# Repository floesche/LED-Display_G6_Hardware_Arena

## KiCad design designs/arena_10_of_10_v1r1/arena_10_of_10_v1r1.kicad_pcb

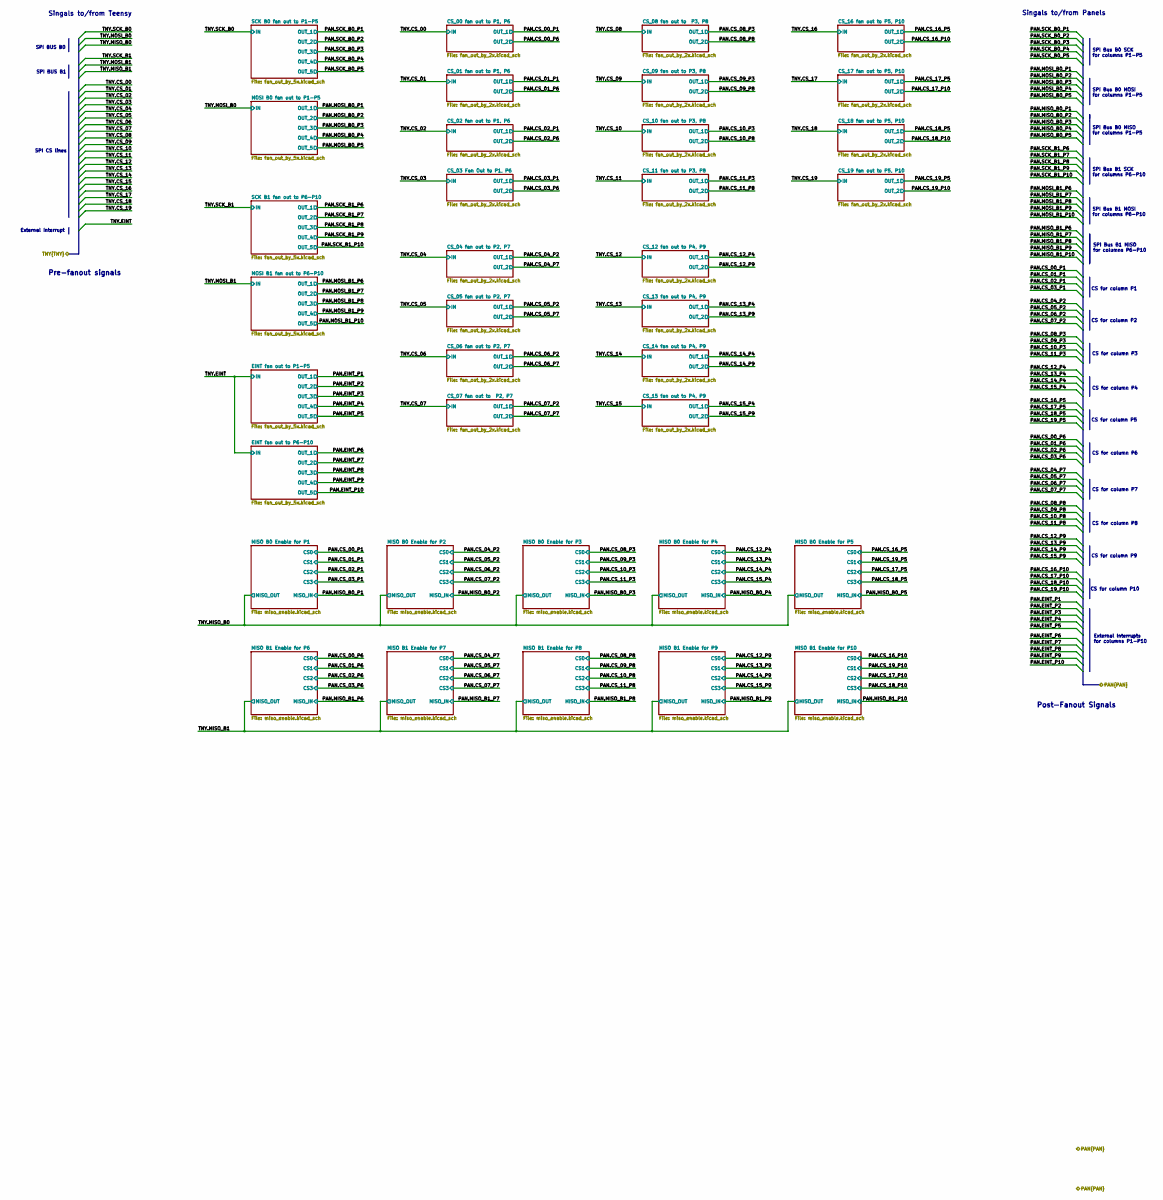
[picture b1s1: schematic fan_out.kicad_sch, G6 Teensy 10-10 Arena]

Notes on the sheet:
Singals to/from Panels
Pre-fanout signals
SPI BUS B0
SPI BUS B1
SPI Bus B1 MOSI for columns P6-P10
SPI Bus B0 SCK for columns P1-P5
SPI Bus B0 MOSI for columns P1-P5
CS for column P1
CS for column P5
CS for column P8
CS for column P3
SPI Bus B1 SCK for columns P6-P10
External Interrupt
External Interrupts for columns P1-P10
CS for column P7
Post-Fanout Signals
CS for column P4
CS for column P10
SPI Bus B0 MISO for columns P1-P5
CS for column P9
CS for column P2
Singals to/from Teensy
SPI Bus B1 MISO for columns P6-P10
SPI CS lines
CS for column P6

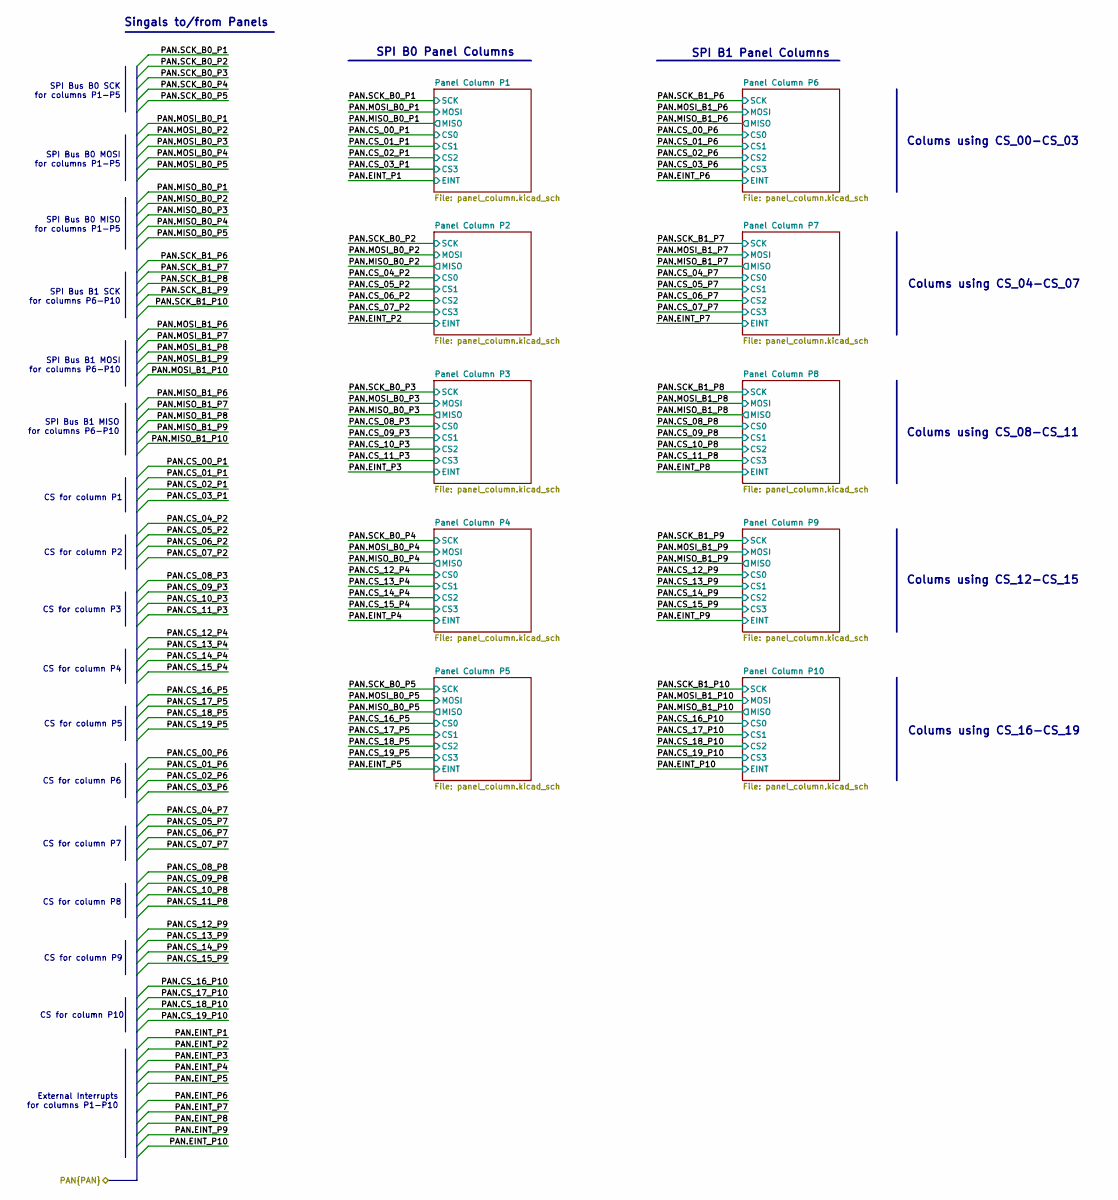
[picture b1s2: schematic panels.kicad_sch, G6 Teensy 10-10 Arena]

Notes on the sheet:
CS for column P2
CS for column P9
SPI Bus B1 MOSI for columns P6-P10
SPI B0 Panel Columns
Colums using CS_00-CS_03
SPI B1 Panel Columns
CS for column P4
SPI Bus B0 MISO for columns P1-P5
SPI Bus B0 MOSI for columns P1-P5
SPI Bus B1 MISO for columns P6-P10
CS for column P7
SPI Bus B0 SCK for columns P1-P5
CS for column P10
Colums using CS_08-CS_11
CS for column P3
Colums using CS_16-CS_19
CS for column P6
Colums using CS_12-CS_15
Colums using CS_04-CS_07
SPI Bus B1 SCK for columns P6-P10
External Interrupts for columns P1-P10
Singals to/from Panels
CS for column P8
CS for column P5
CS for column P1

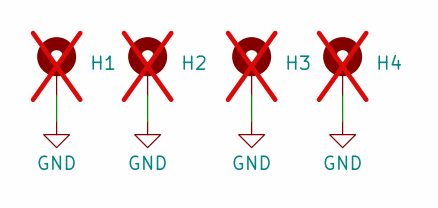
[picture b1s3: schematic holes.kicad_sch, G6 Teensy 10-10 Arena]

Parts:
H1, H2, H3, H4: MountingHole_Pad; MountingHole_4.5mm_Pad; not fitted

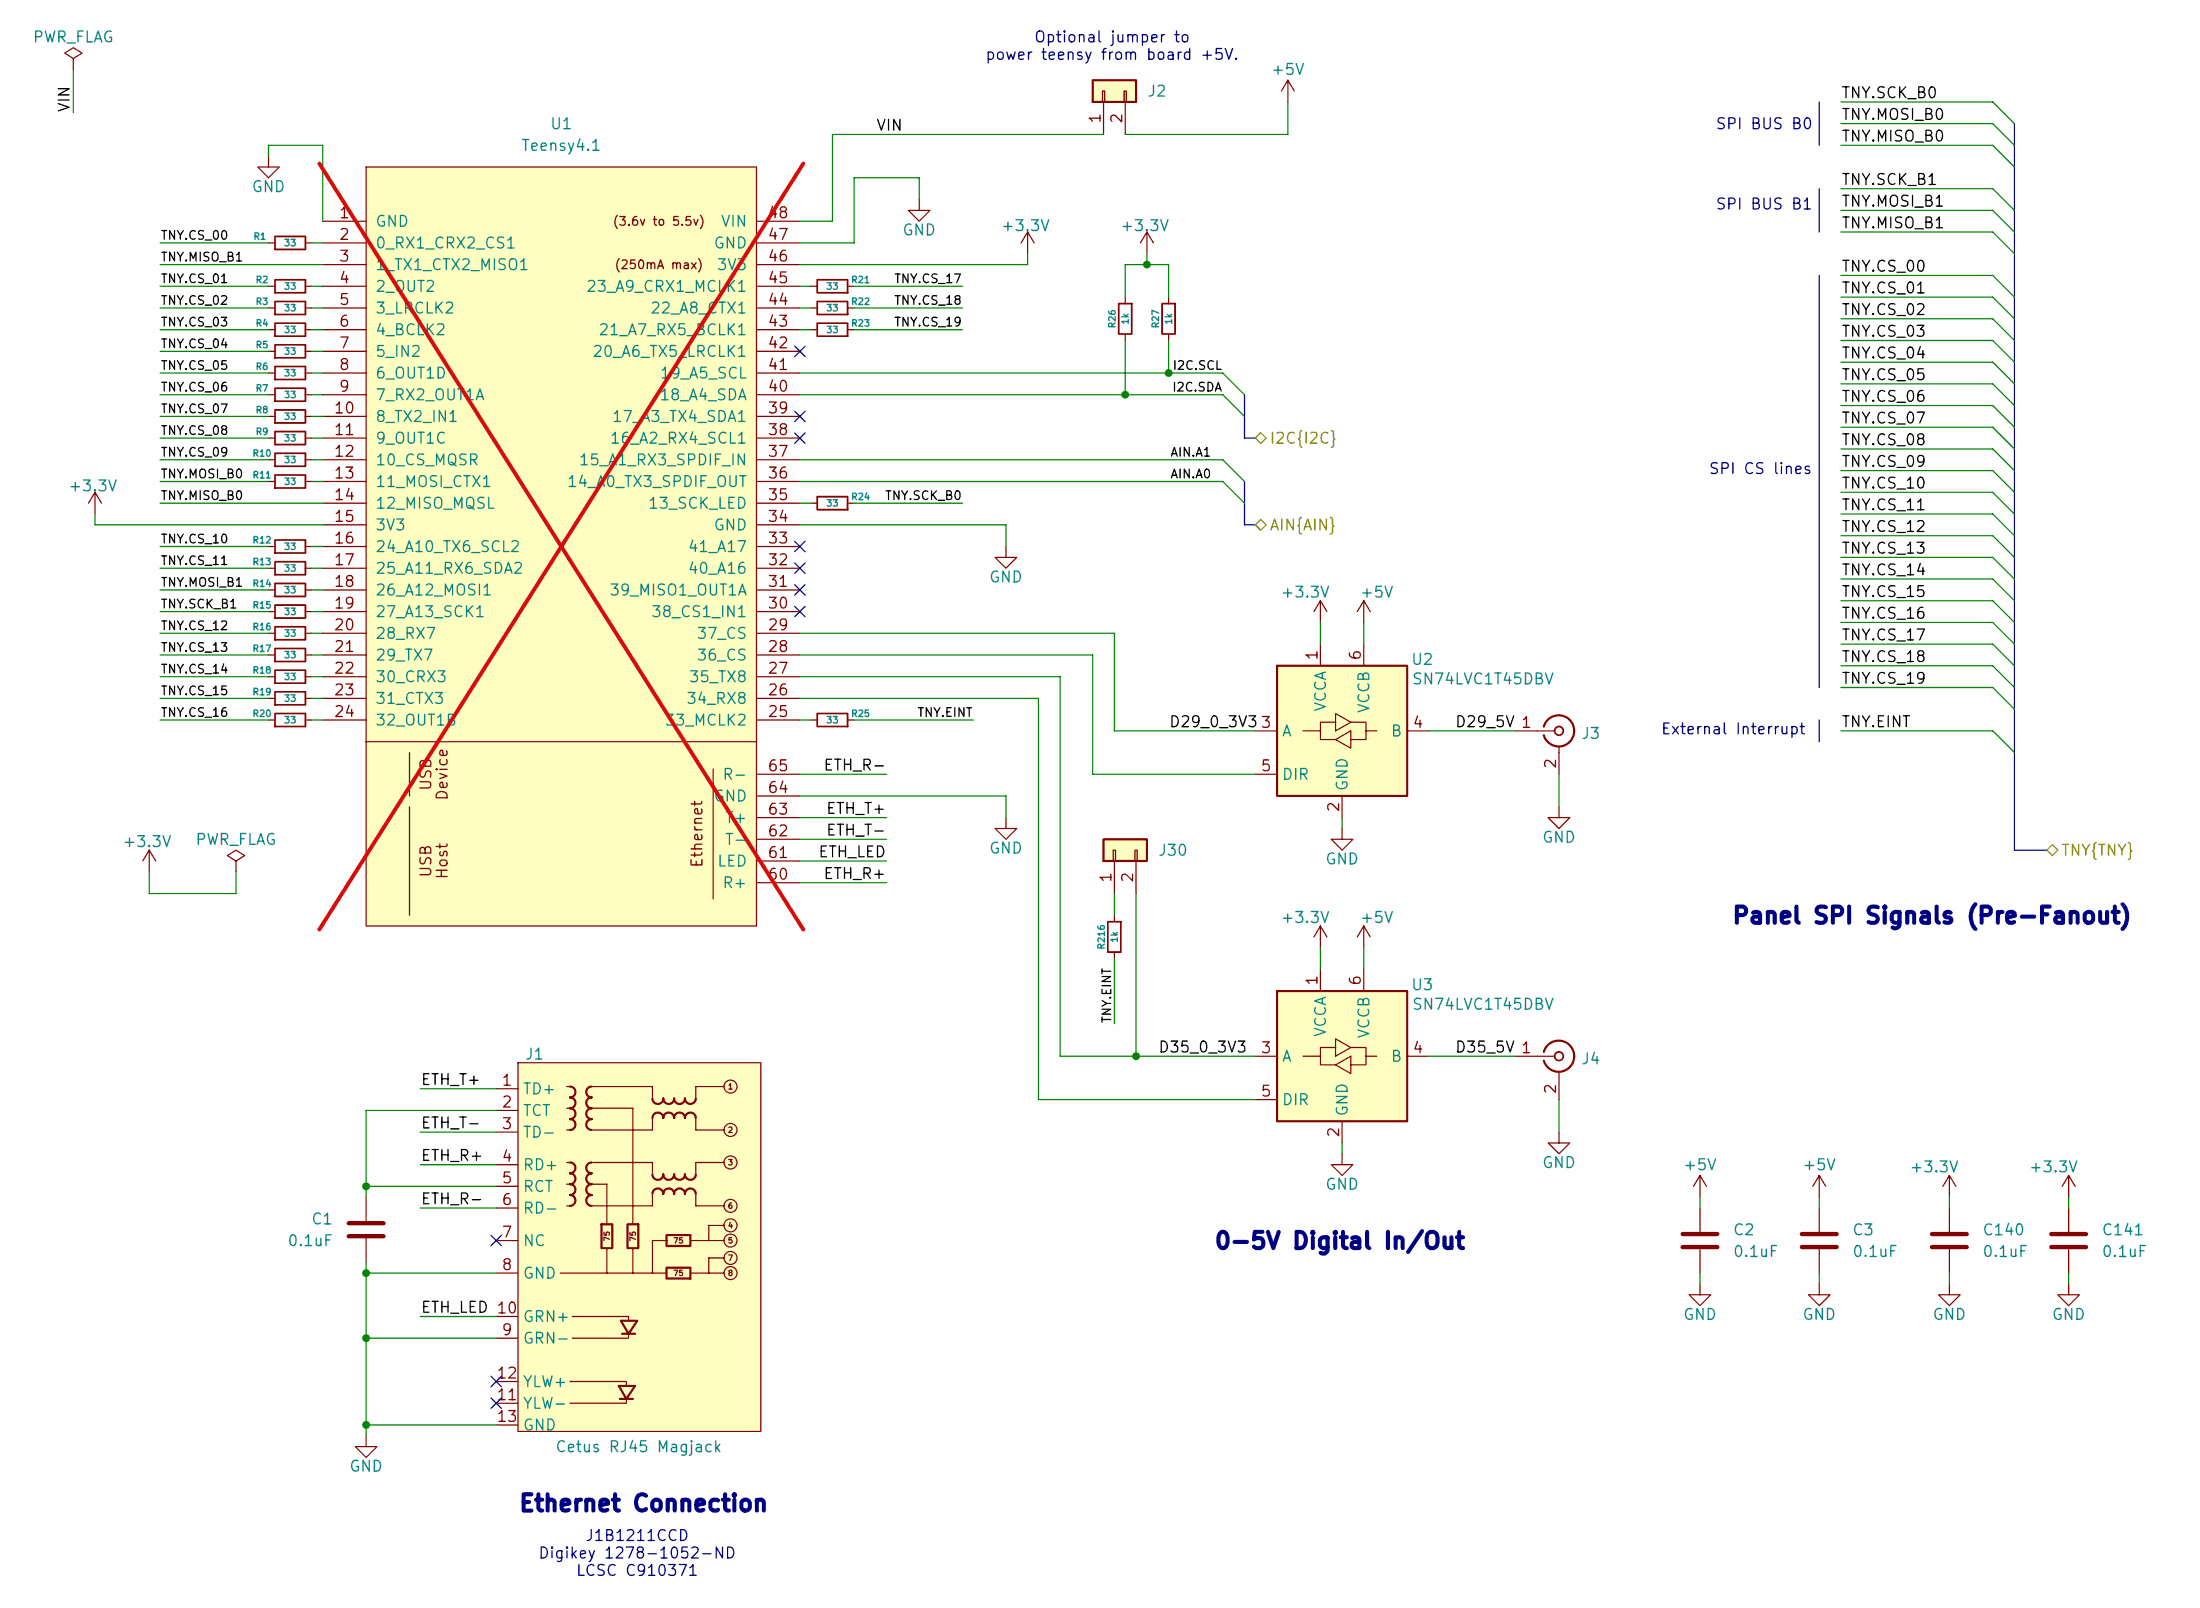
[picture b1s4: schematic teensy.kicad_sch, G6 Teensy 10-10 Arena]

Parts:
C1, C2, C3, C140, C141: 0.1uF; C_0402_1005Metric; LCSC Part # C1525
J1: Cetus RJ45 Magjack; RJ45_Cetus_J1B1211CCD_Horizontal; LCSC Part # C910371
J2, J30: Conn_01x02; PinHeader_1x02_P2.54mm_Vertical; LCSC Part # C124375
J3, J4: Conn_Coaxial; BNC; LCSC Part # C2837587
R1, R2, R3, R4, R5, R6, R7, R8, R9, R10, R11, R12, R13, R14, R15, R16, R17, R18, R19, R20, R21, R22, R23, R24, R25: 33; R_0402_1005Metric; LCSC Part # C25105
R26, R27, R216: 1k; R_0402_1005Metric; LCSC Part # C11702
U1: Teensy4.1; Teensy41_ethernet_only; not fitted
U2, U3: SN74LVC1T45DBV; SOT-23-6; LCSC Part # C7843

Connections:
+3.3V: C140.1, C141.1, R26.1, R27.1, U1.15 (3V3), U1.46 (3V3), U2.1 (VCCA), U3.1 (VCCA); also elsewhere on the board
/Analog IO/AIN.A0: U1.36 (14_A0_TX3_SPDIF_OUT); also elsewhere on the board
/Analog IO/AIN.A1: U1.37 (15_A1_RX3_SPDIF_IN); also elsewhere on the board
/Analog IO/I2C.SCL: R27.2, U1.41 (19_A5_SCL); also elsewhere on the board
/Analog IO/I2C.SDA: R26.2, U1.40 (18_A4_SDA); also elsewhere on the board
/Fan Out/TNY.CS_00: R1.1; also elsewhere on the board
/Fan Out/TNY.CS_01: R2.1; also elsewhere on the board
/Fan Out/TNY.CS_02: R3.1; also elsewhere on the board
/Fan Out/TNY.CS_03: R4.1; also elsewhere on the board
/Fan Out/TNY.CS_04: R5.1; also elsewhere on the board
/Fan Out/TNY.CS_05: R6.1; also elsewhere on the board
/Fan Out/TNY.CS_06: R7.1; also elsewhere on the board
/Fan Out/TNY.CS_07: R8.1; also elsewhere on the board
/Fan Out/TNY.CS_08: R9.1; also elsewhere on the board
/Fan Out/TNY.CS_09: R10.1; also elsewhere on the board
/Fan Out/TNY.CS_10: R12.1; also elsewhere on the board
/Fan Out/TNY.CS_11: R13.1; also elsewhere on the board
/Fan Out/TNY.CS_12: R16.1; also elsewhere on the board
/Fan Out/TNY.CS_13: R17.1; also elsewhere on the board
/Fan Out/TNY.CS_14: R18.1; also elsewhere on the board
/Fan Out/TNY.CS_15: R19.1; also elsewhere on the board
/Fan Out/TNY.CS_16: R20.1; also elsewhere on the board
/Fan Out/TNY.CS_17: R21.1; also elsewhere on the board
/Fan Out/TNY.CS_18: R22.1; also elsewhere on the board
/Fan Out/TNY.CS_19: R23.1; also elsewhere on the board
/Fan Out/TNY.EINT: R25.1, R216.2; also elsewhere on the board
/Fan Out/TNY.MISO_B0: U1.14 (12_MISO_MQSL); also elsewhere on the board
/Fan Out/TNY.MISO_B1: U1.3 (1_TX1_CTX2_MISO1); also elsewhere on the board
/Fan Out/TNY.MOSI_B0: R11.1; also elsewhere on the board
/Fan Out/TNY.MOSI_B1: R14.1; also elsewhere on the board
/Fan Out/TNY.SCK_B0: R24.1; also elsewhere on the board
/Fan Out/TNY.SCK_B1: R15.1; also elsewhere on the board
/Teensy/D36_5V: J3.1 (In), U2.4 (Y)
/Teensy/D37_5V: J4.1 (In), U3.4 (Y)
/Teensy/ETH_LED: J1.10 (GRN+), U1.61 (LED)
/Teensy/ETH_R+: J1.4 (RD+), U1.60 (R+)
/Teensy/ETH_R-: J1.6 (RD-), U1.65 (R-)
/Teensy/ETH_T+: J1.1 (TD+), U1.63 (T+)
/Teensy/ETH_T-: J1.3 (TD-), U1.62 (T-)
/Teensy/VIN: J2.1, U1.48 (VIN)
unnamed: C1.1, J1.2 (TCT), J1.5 (RCT)
unnamed: J30.1, R216.1
unnamed: R1.2, U1.2 (0_RX1_CRX2_CS1)
unnamed: R2.2, U1.4 (2_OUT2)
unnamed: R3.2, U1.5 (3_LRCLK2)
unnamed: R4.2, U1.6 (4_BCLK2)
unnamed: R5.2, U1.7 (5_IN2)
unnamed: R6.2, U1.8 (6_OUT1D)
unnamed: R7.2, U1.9 (7_RX2_OUT1A)
unnamed: R8.2, U1.10 (8_TX2_IN1)
unnamed: R9.2, U1.11 (9_OUT1C)
unnamed: R10.2, U1.12 (10_CS_MQSR)
unnamed: R11.2, U1.13 (11_MOSI_CTX1)
unnamed: R24.2, U1.35 (13_SCK_LED)
unnamed: R23.2, U1.43 (21_A7_RX5_BCLK1)
unnamed: R22.2, U1.44 (22_A8_CTX1)
unnamed: R21.2, U1.45 (23_A9_CRX1_MCLK1)
unnamed: R12.2, U1.16 (24_A10_TX6_SCL2)
unnamed: R13.2, U1.17 (25_A11_RX6_SDA2)
unnamed: R14.2, U1.18 (26_A12_MOSI1)
unnamed: R15.2, U1.19 (27_A13_SCK1)
unnamed: R16.2, U1.20 (28_RX7)
unnamed: R17.2, U1.21 (29_TX7)
unnamed: R18.2, U1.22 (30_CRX3)
unnamed: R19.2, U1.23 (31_CTX3)
unnamed: R20.2, U1.24 (32_OUT1B)
unnamed: R25.2, U1.25 (33_MCLK2)

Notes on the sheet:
Panel SPI Signals (Pre-Fanout)
Optional jumper to power teensy from board +5V.
J1B1211CCD Digikey 1278-1052-ND LCSC C910371
SPI BUS B0
0-5V Digital In/Out
External Interrupt
SPI BUS B1
Ethernet Connection
SPI CS lines

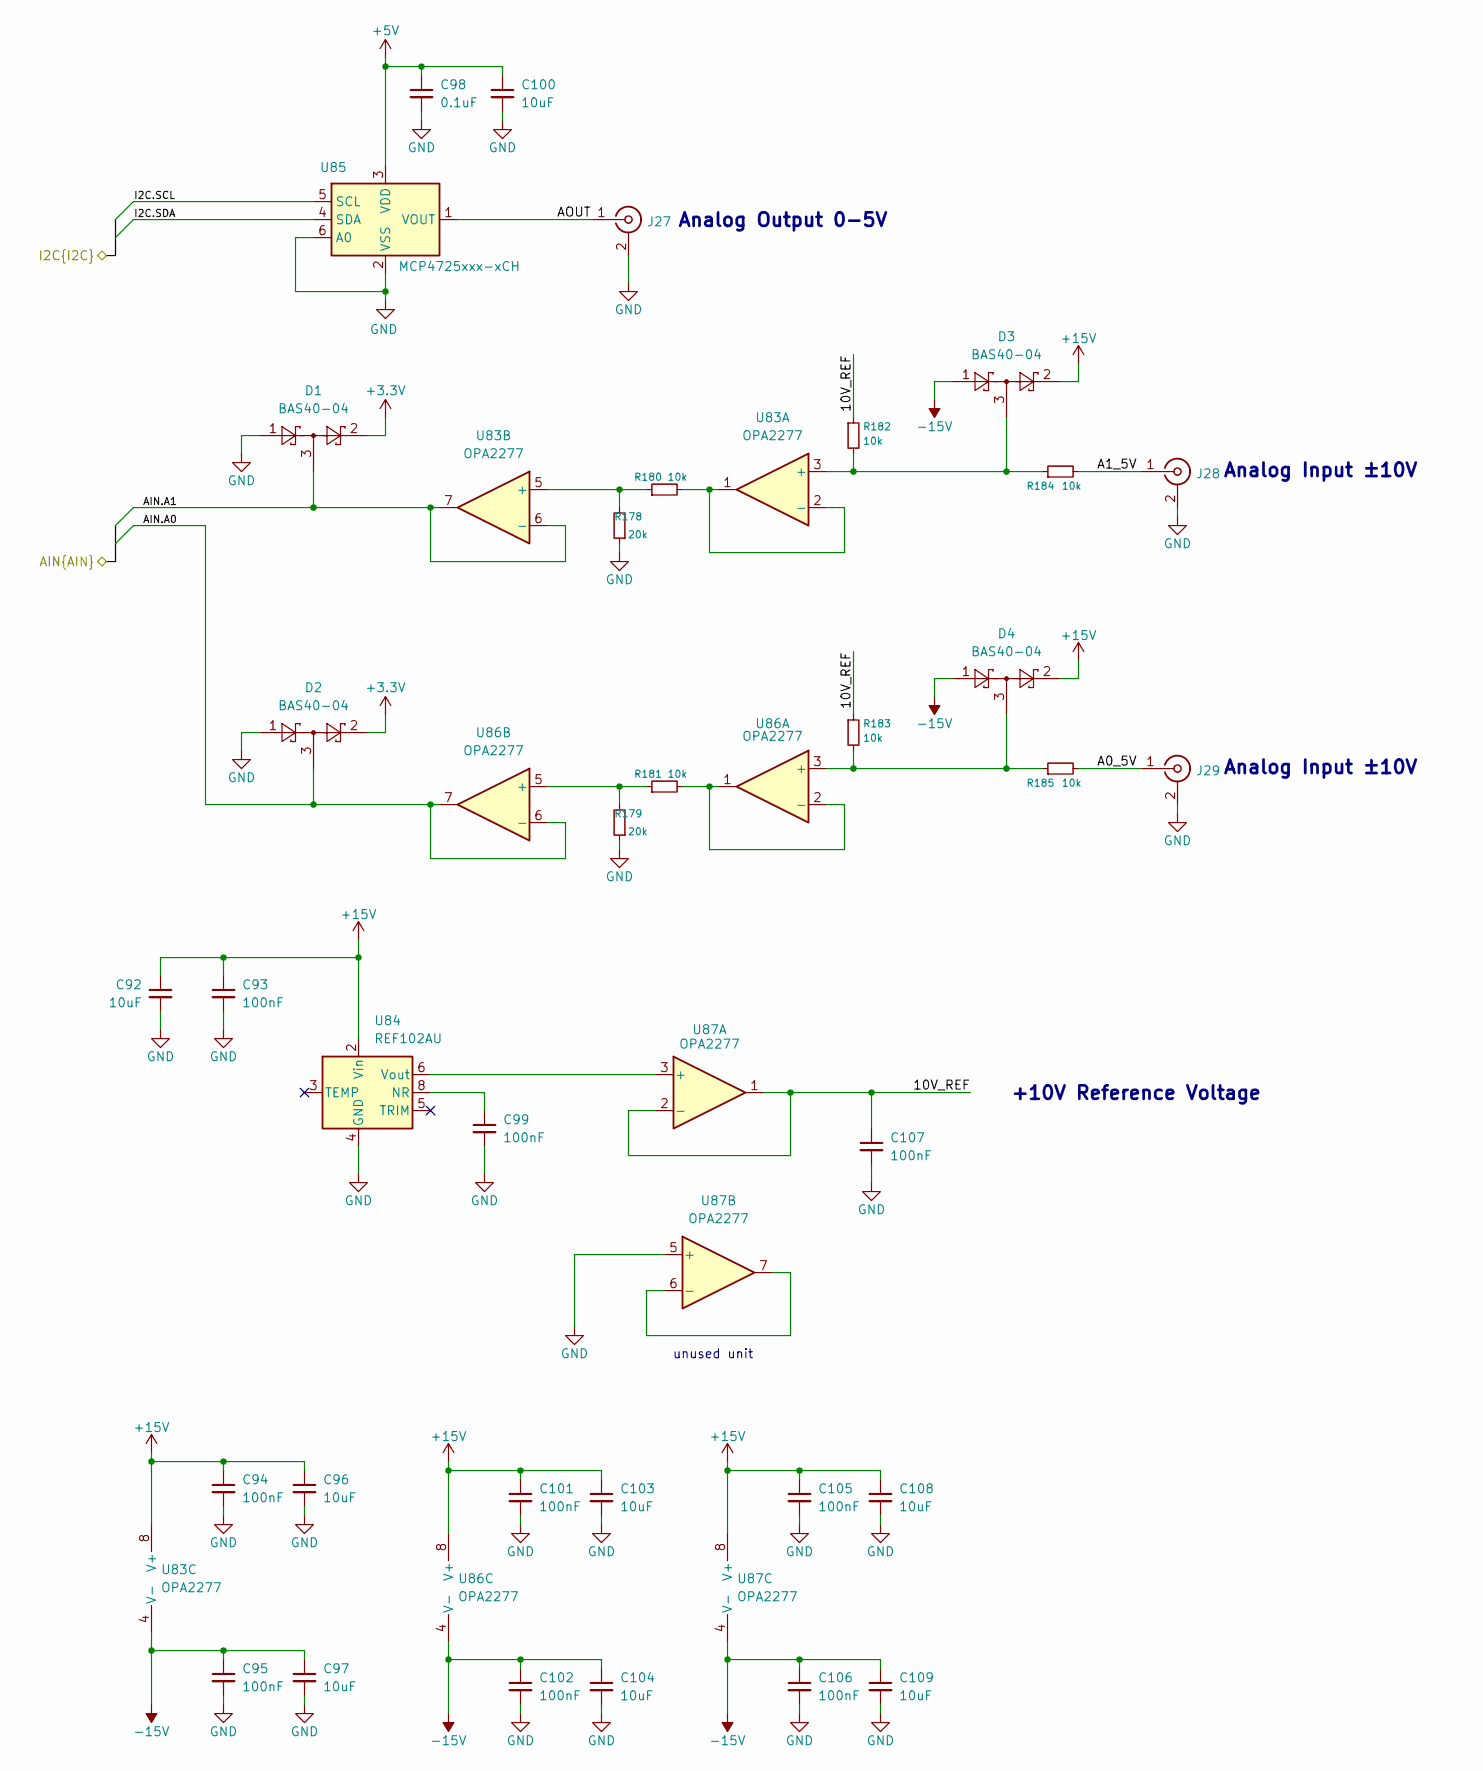
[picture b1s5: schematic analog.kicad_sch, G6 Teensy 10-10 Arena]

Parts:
C92, C96, C97, C100, C103, C104, C108, C109: 10uF; C_1206_3216Metric; LCSC Part # C89632
C93, C94, C95, C99, C101, C102, C105, C106, C107: 100nF; C_0402_1005Metric; LCSC Part # C307331
C98: 0.1uF; C_0402_1005Metric; LCSC Part # C1525
D1, D2, D3, D4: BAS40-04; SOT-23; LCSC Part # C7502688
J27, J28, J29: Conn_Coaxial; BNC; LCSC Part # C2837587
R178, R179: 20k; R_0402_1005Metric; LCSC Part # C705630
R180, R181, R182, R183, R184, R185: 10k; R_0402_1005Metric; LCSC Part # C190095
U83, U86, U87: OPA2277; SOIC-8_3.9x4.9mm_P1.27mm; LCSC Part # C24460
U84: REF102AU; SOIC-8_3.9x4.9mm_P1.27mm; LCSC Part # C81460
U85: MCP4725xxx-xCH; SOT-23-6; LCSC Part # C144198

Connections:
+3.3V: D1.2, D2.2; also elsewhere on the board
+15V: C92.1, C93.1, C94.1, C96.1, C101.1, C103.1, C105.1, C108.1, D3.2, D4.2, U83.8 (V+), U84.2 (Vin), U86.8 (V+), U87.8 (V+); also elsewhere on the board
-15V: C95.1, C97.1, C102.1, C104.1, C106.1, C109.1, D3.1, D4.1, U83.4 (V-), U86.4 (V-), U87.4 (V-); also elsewhere on the board
/Analog IO/10V_REF: C107.1, R182.1, R183.1, U87.1, U87.2 (-)
/Analog IO/A0_5V: J29.1 (In), R185.2
/Analog IO/A1_5V: J28.1 (In), R184.2
/Analog IO/AIN.A0: D2.3, U86.6 (-), U86.7; also elsewhere on the board
/Analog IO/AIN.A1: D1.3, U83.6 (-), U83.7; also elsewhere on the board
/Analog IO/AOUT: J27.1 (In), U85.1 (VOUT)
/Analog IO/I2C.SCL: U85.5 (SCL); also elsewhere on the board
/Analog IO/I2C.SDA: U85.4 (SDA); also elsewhere on the board
unnamed: D3.3, R182.2, R184.1, U83.3 (+)
unnamed: R180.2, U83.1, U83.2 (-)
unnamed: R178.2, R180.1, U83.5 (+)
unnamed: C99.1, U84.8 (NR)
unnamed: U84.6 (Vout), U87.3 (+)
unnamed: D4.3, R183.2, R185.1, U86.3 (+)
unnamed: R181.2, U86.1, U86.2 (-)
unnamed: R179.2, R181.1, U86.5 (+)
unnamed: U87.6 (-), U87.7

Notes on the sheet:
unused unit
+10V Reference Voltage
Analog Output 0-5V
Analog Input ±10V

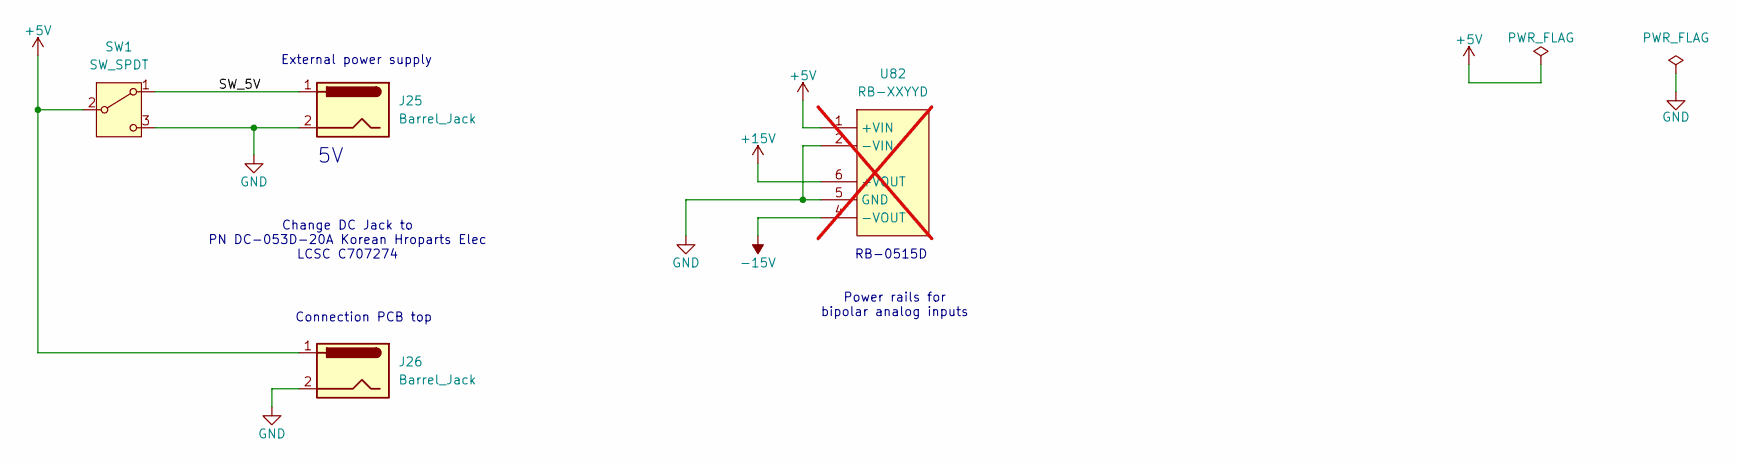
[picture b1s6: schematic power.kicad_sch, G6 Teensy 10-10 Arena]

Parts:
J25, J26: Barrel_Jack; DC-053D-20A; LCSC Part # C707274
SW1: SW_SPDT; slide_switch; LCSC Part # C19189125
U82: RB-XXYYD; RB-XXYYYD; not fitted

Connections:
+15V: U82.6 (+VOUT); also elsewhere on the board
-15V: U82.4 (-VOUT); also elsewhere on the board
/Power/SW_5V: J25.1, SW1.1 (A)

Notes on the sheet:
Change DC Jack to PN DC-053D-20A Korean Hroparts Elec LCSC C707274
External power supply
Power rails for bipolar analog inputs
Connection PCB top
RB-0515D

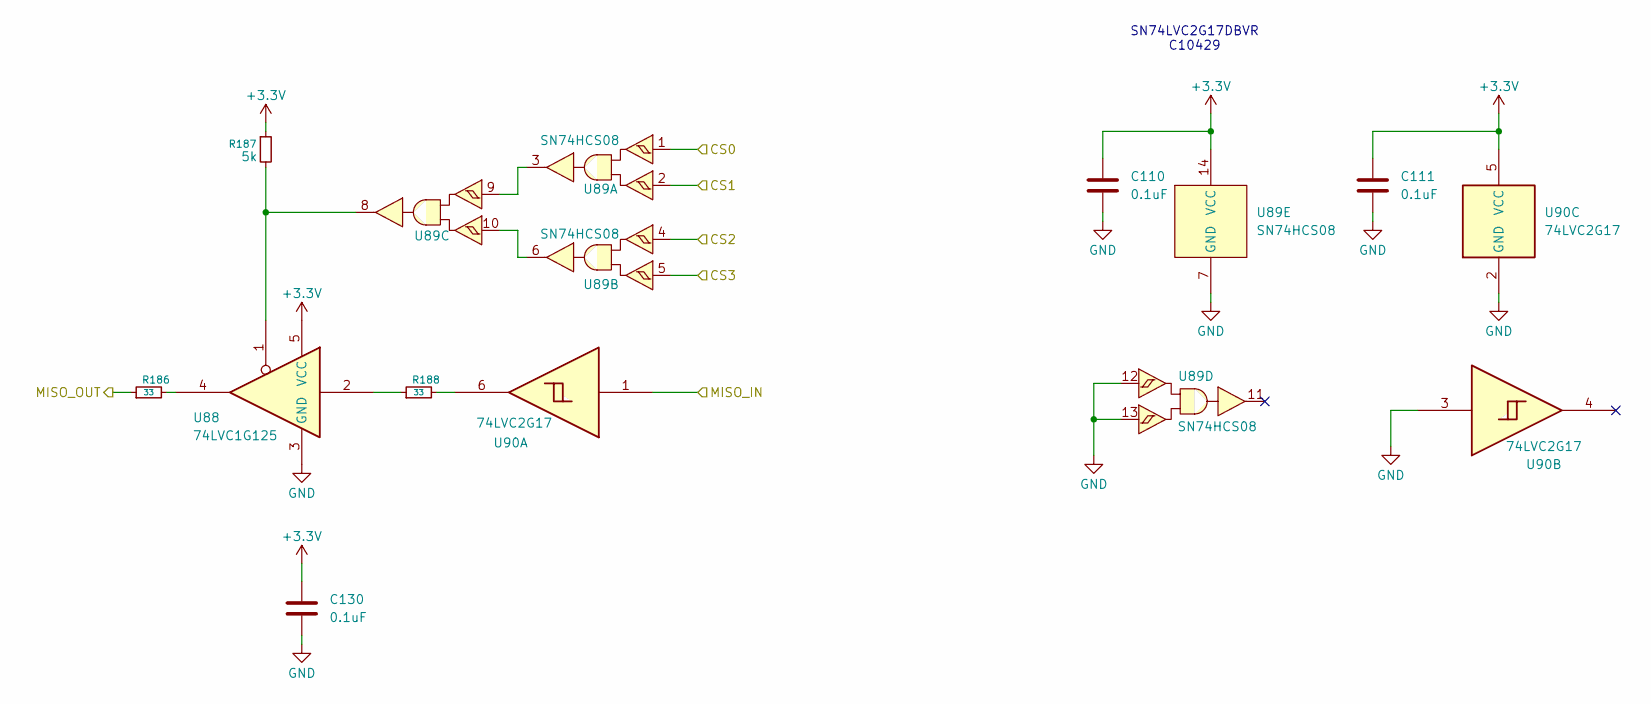
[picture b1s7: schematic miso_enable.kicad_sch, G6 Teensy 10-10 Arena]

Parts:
C110, C111, C130: 0.1uF; C_0402_1005Metric; LCSC Part # C1525
R186, R188: 33; R_0402_1005Metric; LCSC Part # C25105
R187: 5k; R_0402_1005Metric; LCSC Part # C5948099
U88: 74LVC1G125; SOT-23-5; LCSC Part # C7394017
U89: SN74HCS08; SOIC-14_3.9x8.7mm_P1.27mm; LCSC Part # C2868021
U90: 74LVC2G17; SOT-23-6; LCSC Part # C7394037

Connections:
+3.3V: C110.1, C111.1, C130.1, R187.1, U88.5 (VCC), U89.14 (VCC), U90.5 (VCC); also elsewhere on the board
/Fan Out/PAN.CS_00_P1: U89.1; also elsewhere on the board
/Fan Out/PAN.CS_01_P1: U89.2; also elsewhere on the board
/Fan Out/PAN.CS_02_P1: U89.4; also elsewhere on the board
/Fan Out/PAN.CS_03_P1: U89.5; also elsewhere on the board
/Fan Out/PAN.MISO_B0_P1: U90.1; also elsewhere on the board
/Fan Out/TNY.MISO_B0: R186.1; also elsewhere on the board
unnamed: R186.2, U88.4
unnamed: R187.2, U88.1, U89.8
unnamed: R188.1, U88.2
unnamed: R188.2, U90.6
unnamed: U89.3, U89.9
unnamed: U89.6, U89.10

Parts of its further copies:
C112, C113, C114, C115, C116, C117, C118, C119, C120, C121, C122, C123, C124, C125, C126, C127, C128, C129, C131, C132, C133, C134, C135, C136, C137, C138, C139: 0.1uF; C_0402_1005Metric; LCSC Part # C1525
R189, R191, R192, R194, R195, R197, R198, R200, R201, R203, R204, R206, R207, R209, R210, R212, R213, R215: 33; R_0402_1005Metric; LCSC Part # C25105
R190, R193, R196, R199, R202, R205, R208, R211, R214: 5k; R_0402_1005Metric; LCSC Part # C5948099
U91, U94, U95, U98, U99, U102, U103, U106, U107: SN74HCS08; SOIC-14_3.9x8.7mm_P1.27mm; LCSC Part # C2868021
U92, U96, U100, U104, U108, U112, U116, U120, U124: 74LVC1G125; SOT-23-5; LCSC Part # C7394017
U93, U97, U101, U105, U109, U113, U117, U121, U125: 74LVC2G17; SOT-23-6; LCSC Part # C7394037

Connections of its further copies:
+3.3V: C112.1, C113.1, C114.1, C115.1, C116.1, C117.1, C118.1, C119.1, C120.1, C121.1, C122.1, C123.1, C124.1, C125.1, C126.1, C127.1, C128.1, C129.1, C131.1, C132.1, C133.1, C134.1, C135.1, C136.1, C137.1, C138.1, C139.1, R190.1, R193.1, R196.1, R199.1, R202.1, R205.1, R208.1, R211.1, R214.1, U91.14 (VCC), U92.5 (VCC), U93.5 (VCC), U94.14 (VCC), U95.14 (VCC), U96.5 (VCC), U97.5 (VCC), U98.14 (VCC), U99.14 (VCC), U100.5 (VCC), U101.5 (VCC), U102.14 (VCC), U103.14 (VCC), U104.5 (VCC), U105.5 (VCC), U106.14 (VCC), U107.14 (VCC), U108.5 (VCC), U109.5 (VCC), U112.5 (VCC), U113.5 (VCC), U116.5 (VCC), U117.5 (VCC), U120.5 (VCC), U121.5 (VCC), U124.5 (VCC), U125.5 (VCC); also elsewhere on the board
/Fan Out/PAN.CS_00_P6: U99.1; also elsewhere on the board
/Fan Out/PAN.CS_01_P6: U99.2; also elsewhere on the board
/Fan Out/PAN.CS_02_P6: U99.4; also elsewhere on the board
/Fan Out/PAN.CS_03_P6: U99.5; also elsewhere on the board
/Fan Out/PAN.CS_04_P2: U91.1; also elsewhere on the board
/Fan Out/PAN.CS_04_P7: U102.1; also elsewhere on the board
/Fan Out/PAN.CS_05_P2: U91.2; also elsewhere on the board
/Fan Out/PAN.CS_05_P7: U102.2; also elsewhere on the board
/Fan Out/PAN.CS_06_P2: U91.4; also elsewhere on the board
/Fan Out/PAN.CS_06_P7: U102.4; also elsewhere on the board
/Fan Out/PAN.CS_07_P2: U91.5; also elsewhere on the board
/Fan Out/PAN.CS_07_P7: U102.5; also elsewhere on the board
/Fan Out/PAN.CS_08_P3: U94.1; also elsewhere on the board
/Fan Out/PAN.CS_08_P8: U103.1; also elsewhere on the board
/Fan Out/PAN.CS_09_P3: U94.2; also elsewhere on the board
/Fan Out/PAN.CS_09_P8: U103.2; also elsewhere on the board
/Fan Out/PAN.CS_10_P3: U94.4; also elsewhere on the board
/Fan Out/PAN.CS_10_P8: U103.4; also elsewhere on the board
/Fan Out/PAN.CS_11_P3: U94.5; also elsewhere on the board
/Fan Out/PAN.CS_11_P8: U103.5; also elsewhere on the board
/Fan Out/PAN.CS_12_P4: U95.1; also elsewhere on the board
/Fan Out/PAN.CS_12_P9: U106.1; also elsewhere on the board
/Fan Out/PAN.CS_13_P4: U95.2; also elsewhere on the board
/Fan Out/PAN.CS_13_P9: U106.2; also elsewhere on the board
/Fan Out/PAN.CS_14_P4: U95.4; also elsewhere on the board
/Fan Out/PAN.CS_14_P9: U106.4; also elsewhere on the board
/Fan Out/PAN.CS_15_P4: U95.5; also elsewhere on the board
/Fan Out/PAN.CS_15_P9: U106.5; also elsewhere on the board
/Fan Out/PAN.CS_16_P5: U98.1; also elsewhere on the board
/Fan Out/PAN.CS_16_P10: U107.1; also elsewhere on the board
/Fan Out/PAN.CS_17_P5: U98.4; also elsewhere on the board
/Fan Out/PAN.CS_17_P10: U107.4; also elsewhere on the board
/Fan Out/PAN.CS_18_P5: U98.5; also elsewhere on the board
/Fan Out/PAN.CS_18_P10: U107.5; also elsewhere on the board
/Fan Out/PAN.CS_19_P5: U98.2; also elsewhere on the board
/Fan Out/PAN.CS_19_P10: U107.2; also elsewhere on the board
/Fan Out/PAN.MISO_B0_P2: U93.1; also elsewhere on the board
/Fan Out/PAN.MISO_B0_P3: U97.1; also elsewhere on the board
/Fan Out/PAN.MISO_B0_P4: U101.1; also elsewhere on the board
/Fan Out/PAN.MISO_B0_P5: U105.1; also elsewhere on the board
/Fan Out/PAN.MISO_B1_P6: U109.1; also elsewhere on the board
/Fan Out/PAN.MISO_B1_P7: U113.1; also elsewhere on the board
/Fan Out/PAN.MISO_B1_P8: U117.1; also elsewhere on the board
/Fan Out/PAN.MISO_B1_P9: U121.1; also elsewhere on the board
/Fan Out/PAN.MISO_B1_P10: U125.1; also elsewhere on the board
/Fan Out/TNY.MISO_B0: R189.1, R192.1, R195.1, R198.1; also elsewhere on the board
/Fan Out/TNY.MISO_B1: R201.1, R204.1, R207.1, R210.1, R213.1; also elsewhere on the board
unnamed: R189.2, U92.4
unnamed: R190.2, U91.8, U92.1
unnamed: R191.1, U92.2
unnamed: R191.2, U93.6
unnamed: R192.2, U96.4
unnamed: R193.2, U94.8, U96.1
unnamed: R194.1, U96.2
unnamed: R194.2, U97.6
unnamed: R195.2, U100.4
unnamed: R196.2, U95.8, U100.1
unnamed: R197.1, U100.2
unnamed: R197.2, U101.6
unnamed: R198.2, U104.4
unnamed: R199.2, U98.8, U104.1
unnamed: R200.1, U104.2
unnamed: R200.2, U105.6
unnamed: R201.2, U108.4
unnamed: R202.2, U99.8, U108.1
unnamed: R203.1, U108.2
unnamed: R203.2, U109.6
unnamed: R204.2, U112.4
unnamed: R205.2, U102.8, U112.1
unnamed: R206.1, U112.2
unnamed: R206.2, U113.6
unnamed: R207.2, U116.4
unnamed: R208.2, U103.8, U116.1
unnamed: R209.1, U116.2
unnamed: R209.2, U117.6
unnamed: R210.2, U120.4
unnamed: R211.2, U106.8, U120.1
unnamed: R212.1, U120.2
unnamed: R212.2, U121.6
unnamed: R213.2, U124.4
unnamed: R214.2, U107.8, U124.1
unnamed: R215.1, U124.2
unnamed: R215.2, U125.6
unnamed: U91.3, U91.9
unnamed: U91.6, U91.10
unnamed: U94.3, U94.9
unnamed: U94.6, U94.10
unnamed: U95.3, U95.9
unnamed: U95.6, U95.10
unnamed: U98.3, U98.9
unnamed: U98.6, U98.10
unnamed: U99.3, U99.9
unnamed: U99.6, U99.10
unnamed: U102.3, U102.9
unnamed: U102.6, U102.10
unnamed: U103.3, U103.9
unnamed: U103.6, U103.10
unnamed: U106.3, U106.9
unnamed: U106.6, U106.10
unnamed: U107.3, U107.9
unnamed: U107.6, U107.10

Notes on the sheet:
SN74LVC2G17DBVR C10429
